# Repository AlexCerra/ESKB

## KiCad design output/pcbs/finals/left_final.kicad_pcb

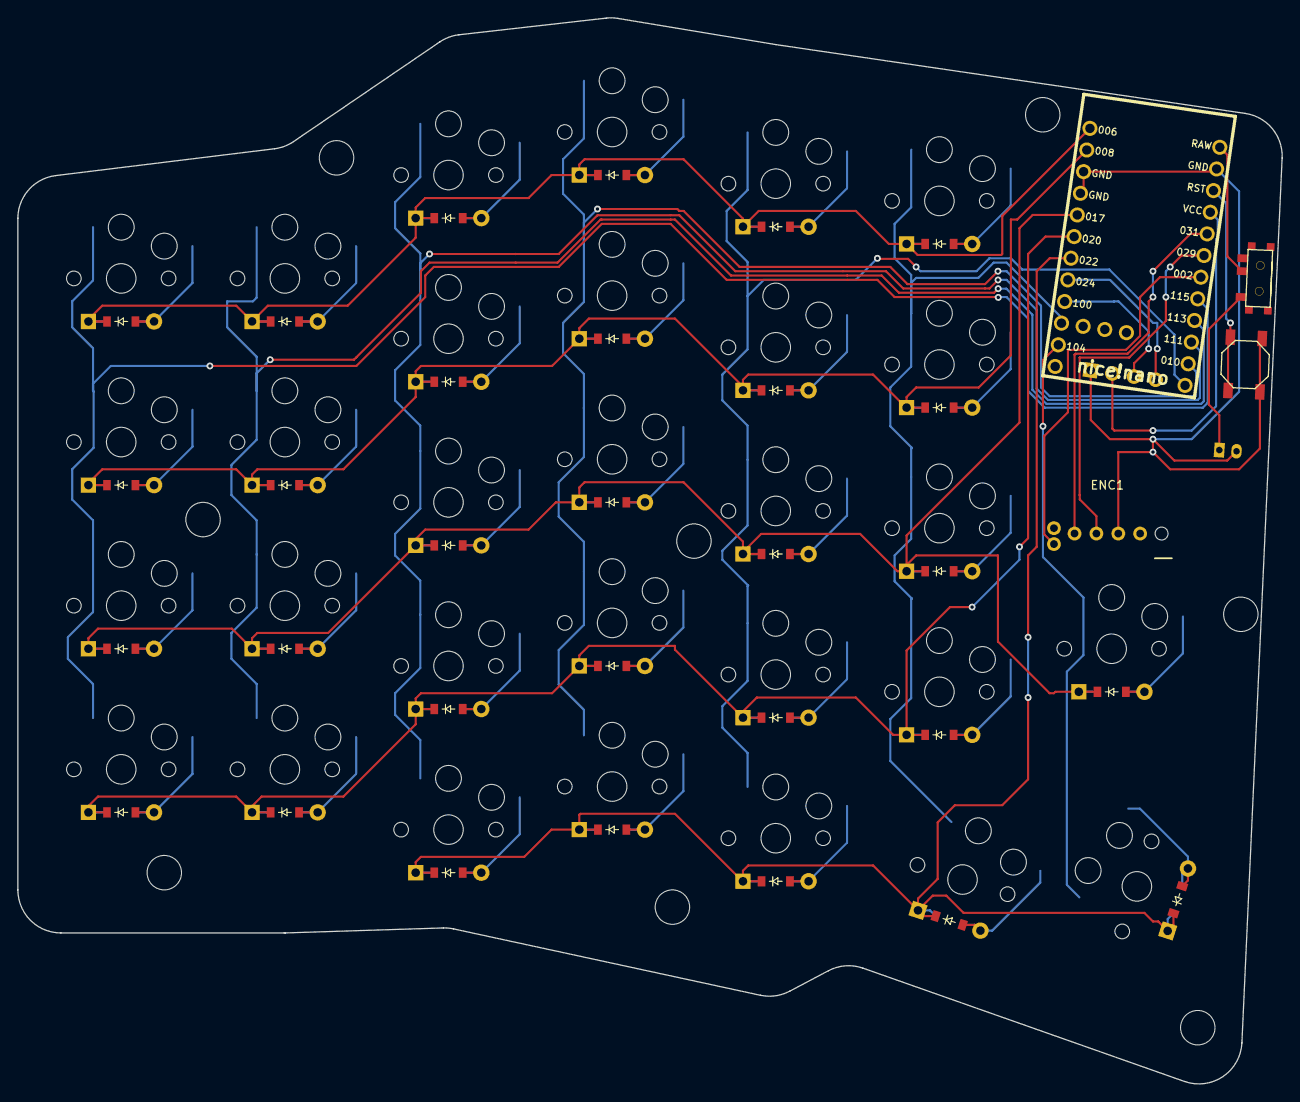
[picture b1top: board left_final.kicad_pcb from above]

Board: 2 copper layers, 146.8 x 123.8 mm, 66 parts (0 on the bottom side), 52 nets.

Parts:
B1: SW_TACT_ALPS_SKQGABE010
D1, D2, D3, D4, D5, D6, D7, D8, D9, D10, D11, D12, D13, D14, D15, D16, D17, D18, D19, D20, D21, D22, D23, D24, D25, D26, D27, D28, D29, D30: ComboDiode
ENC1: RollerEncoder_Panasonic_EVQWGD001; Panasonic_EVQWGD001
JST1: JST_PH_S2B-PH-K_02x2.00mm_Angled
MCU1: nice_nano
OLED1: OLED; OLED_headers
S1, S2, S3, S4, S5, S6, S7, S8, S9, S10, S11, S12, S13, S14, S15, S16, S17, S18, S19, S20, S21, S22, S23, S24, S25, S26, S27, S28, S29, S30: PG1350
T1: SPDT_C128955

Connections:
GND: B1.1, ENC1.C, JST1.2, MCU1.3, MCU1.4, MCU1.23, OLED1.1
P002: ENC1.S1, MCU1.18
P006: D4.1, D8.1, D13.1, D18.1, D23.1, D27.1, MCU1.1
P008: D3.1, D7.1, D12.1, D17.1, D22.1, D26.1, MCU1.2
P009: MCU1.13, S19.1, S20.1, S21.1, S22.1, S23.1
P010: MCU1.14, S14.1, S15.1, S16.1, S17.1, S18.1
P011: MCU1.10, S24.1, S25.1, S26.1, S27.1, S29.1
P017: D2.1, D6.1, D11.1, D16.1, D21.1, D25.1, D28.1, MCU1.5
P020: D1.1, D5.1, D10.1, D15.1, D20.1, D24.1, MCU1.6
P022: D9.1, D14.1, D19.1, D29.1, D30.1, MCU1.7
P024: MCU1.8, OLED1.4
P029: ENC1.B, MCU1.19
P031: ENC1.A, MCU1.20
P100: MCU1.9, OLED1.3
P104: MCU1.11, S28.1, S30.1
P111: MCU1.15, S9.1, S10.1, S11.1, S12.1, S13.1
P113: MCU1.16, S5.1, S6.1, S7.1, S8.1
P115: MCU1.17, S1.1, S2.1, S3.1, S4.1
RAW: MCU1.24, T1.2
RST: B1.2, MCU1.22
VCC: MCU1.21, OLED1.2
far_cluster: D30.2, S30.2
home_cluster: D29.2, S29.2
index_bottom: D20.2, S20.2
index_home: D21.2, S21.2
index_mod: D19.2, S19.2
index_num: D23.2, S23.2
index_top: D22.2, S22.2
inner_bottom: D24.2, S24.2
inner_home: D25.2, S25.2
inner_mod_home: D28.2, S28.2
inner_num: D27.2, S27.2
inner_top: D26.2, S26.2
middle_bottom: D15.2, S15.2
middle_home: D16.2, S16.2
middle_mod: D14.2, S14.2
middle_num: D18.2, S18.2
middle_top: D17.2, S17.2
outer_bottom: D1.2, S1.2
outer_home: D2.2, S2.2
outer_num: D4.2, S4.2
outer_top: D3.2, S3.2
pinky_bottom: D5.2, S5.2
pinky_home: D6.2, S6.2
pinky_num: D8.2, S8.2
pinky_top: D7.2, S7.2
pos: JST1.1, T1.1
ring_bottom: D10.2, S10.2
ring_home: D11.2, S11.2
ring_mod: D9.2, S9.2
ring_num: D13.2, S13.2
ring_top: D12.2, S12.2

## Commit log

2025-02-22 adjusted small changes, made right board
2025-02-23 updates to PCBS. some edits but mostly done PCBs
